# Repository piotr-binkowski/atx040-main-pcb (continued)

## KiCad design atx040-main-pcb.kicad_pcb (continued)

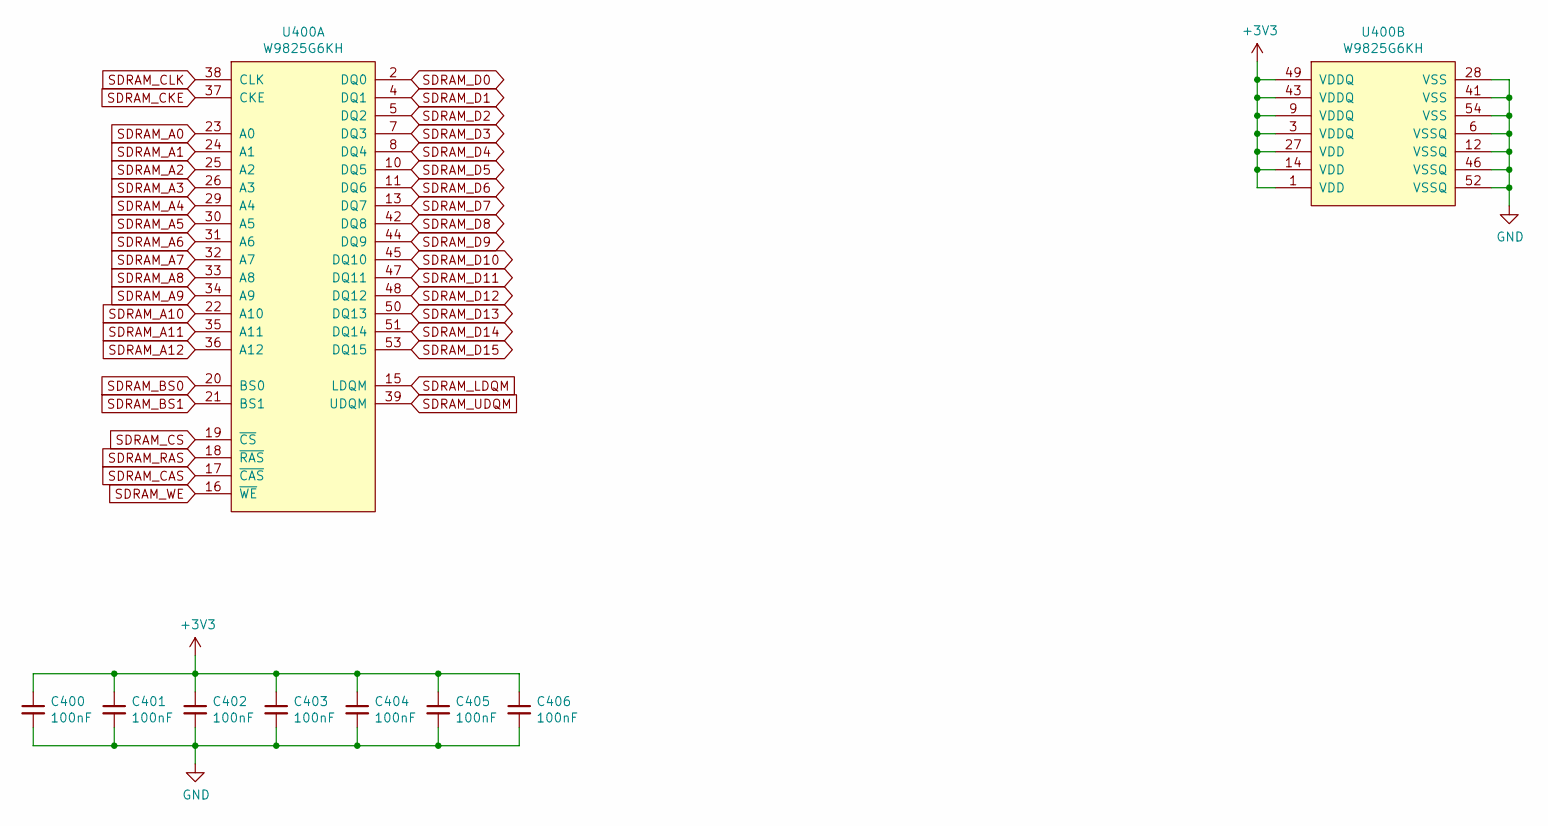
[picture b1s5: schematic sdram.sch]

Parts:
C400, C401, C402, C403, C404, C405, C406: 100nF; C_0603_1608Metric
U400: W9825G6KH; TSOP-II-54_22.2x10.16mm_P0.8mm; LCSC C26393

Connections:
+3V3: C400.1, C401.1, C402.1, C403.1, C404.1, C405.1, C406.1, U400.1 (VDD), U400.3 (VDDQ), U400.9 (VDDQ), U400.14 (VDD), U400.27 (VDD), U400.43 (VDDQ), U400.49 (VDDQ); also elsewhere on the board
GND: C400.2, C401.2, C402.2, C403.2, C404.2, C405.2, C406.2, U400.6 (VSSQ), U400.12 (VSSQ), U400.28 (VSS), U400.41 (VSS), U400.46 (VSSQ), U400.52 (VSSQ), U400.54 (VSS); also elsewhere on the board
SDRAM_A0: U400.23 (A0); also elsewhere on the board
SDRAM_A1: U400.24 (A1); also elsewhere on the board
SDRAM_A2: U400.25 (A2); also elsewhere on the board
SDRAM_A3: U400.26 (A3); also elsewhere on the board
SDRAM_A4: U400.29 (A4); also elsewhere on the board
SDRAM_A5: U400.30 (A5); also elsewhere on the board
SDRAM_A6: U400.31 (A6); also elsewhere on the board
SDRAM_A7: U400.32 (A7); also elsewhere on the board
SDRAM_A8: U400.33 (A8); also elsewhere on the board
SDRAM_A9: U400.34 (A9); also elsewhere on the board
SDRAM_A10: U400.22 (A10); also elsewhere on the board
SDRAM_A11: U400.35 (A11); also elsewhere on the board
SDRAM_A12: U400.36 (A12); also elsewhere on the board
SDRAM_BS0: U400.20 (BS0); also elsewhere on the board
SDRAM_BS1: U400.21 (BS1); also elsewhere on the board
SDRAM_CAS: U400.17 (~CAS); also elsewhere on the board
SDRAM_CKE: U400.37 (CKE); also elsewhere on the board
SDRAM_CLK: U400.38 (CLK); also elsewhere on the board
SDRAM_CS: U400.19 (~CS); also elsewhere on the board
SDRAM_D0: U400.2 (DQ0); also elsewhere on the board
SDRAM_D1: U400.4 (DQ1); also elsewhere on the board
SDRAM_D2: U400.5 (DQ2); also elsewhere on the board
SDRAM_D3: U400.7 (DQ3); also elsewhere on the board
SDRAM_D4: U400.8 (DQ4); also elsewhere on the board
SDRAM_D5: U400.10 (DQ5); also elsewhere on the board
SDRAM_D6: U400.11 (DQ6); also elsewhere on the board
SDRAM_D7: U400.13 (DQ7); also elsewhere on the board
SDRAM_D8: U400.42 (DQ8); also elsewhere on the board
SDRAM_D9: U400.44 (DQ9); also elsewhere on the board
SDRAM_D10: U400.45 (DQ10); also elsewhere on the board
SDRAM_D11: U400.47 (DQ11); also elsewhere on the board
SDRAM_D12: U400.48 (DQ12); also elsewhere on the board
SDRAM_D13: U400.50 (DQ13); also elsewhere on the board
SDRAM_D14: U400.51 (DQ14); also elsewhere on the board
SDRAM_D15: U400.53 (DQ15); also elsewhere on the board
SDRAM_LDQM: U400.15 (LDQM); also elsewhere on the board
SDRAM_RAS: U400.18 (~RAS); also elsewhere on the board
SDRAM_UDQM: U400.39 (UDQM); also elsewhere on the board
SDRAM_WE: U400.16 (~WE); also elsewhere on the board

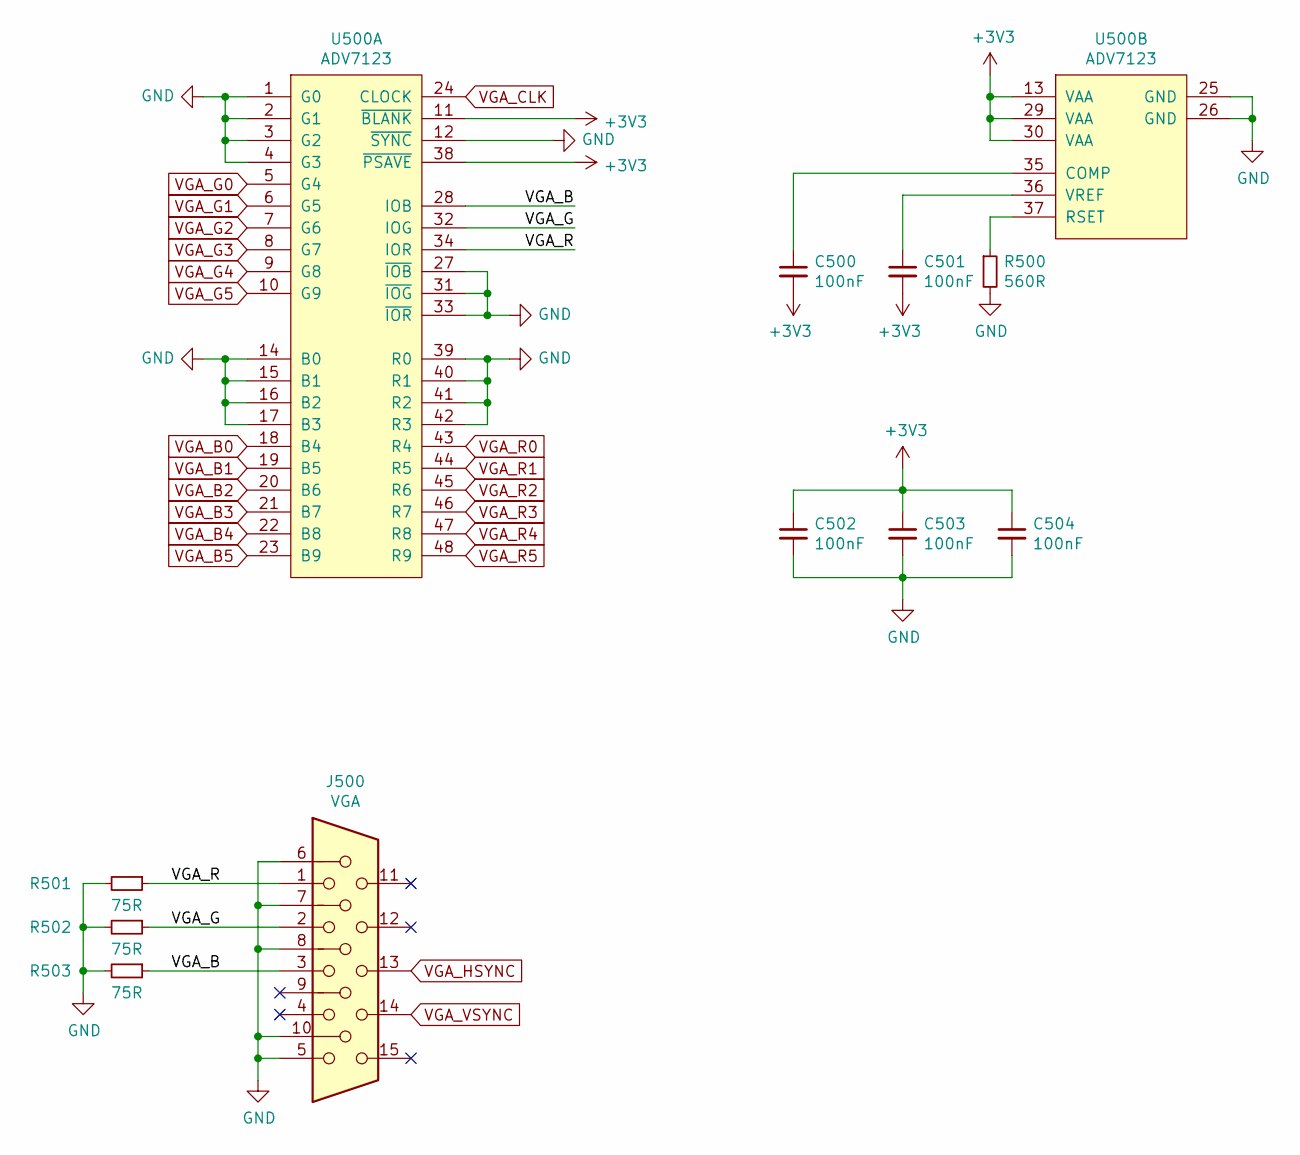
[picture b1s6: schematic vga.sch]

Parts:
C500, C501, C502, C503, C504: 100nF; C_0603_1608Metric
J500: VGA; DSUB-15-HD_Female_Horizontal_P2.29x1.98mm_EdgePinOffset3.03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
R500: 560R; R_0402_1005Metric
R501, R502, R503: 75R; R_0603_1608Metric
U500: ADV7123; LQFP-48_7x7mm_P0.5mm; LCSC C22234

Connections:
+3V3: C500.2, C501.2, C502.1, C503.1, C504.1, U500.11 (~BLANK), U500.13 (VAA), U500.29 (VAA), U500.30 (VAA), U500.38 (~PSAVE); also elsewhere on the board
/VGA Output/VGA_B: J500.3, R503.1, U500.28 (IOB)
/VGA Output/VGA_G: J500.2, R502.1, U500.32 (IOG)
/VGA Output/VGA_R: J500.1, R501.1, U500.34 (IOR)
GND: C502.2, C503.2, C504.2, J500.5, J500.6, J500.7, J500.8, J500.10, R500.2, R501.2, R502.2, R503.2, U500.1 (G0), U500.2 (G1), U500.3 (G2), U500.4 (G3), U500.12 (~SYNC), U500.14 (B0), U500.15 (B1), U500.16 (B2), U500.17 (B3), U500.25 (GND), U500.26 (GND), U500.27 (~IOB), U500.31 (~IOG), U500.33 (~IOR), U500.39 (R0), U500.40 (R1), U500.41 (R2), U500.42 (R3); also elsewhere on the board
unnamed: C500.1, U500.35 (COMP)
unnamed: C501.1, U500.36 (VREF)
unnamed: R500.1, U500.37 (RSET)
VGA_B0: U500.18 (B4); also elsewhere on the board
VGA_B1: U500.19 (B5); also elsewhere on the board
VGA_B2: U500.20 (B6); also elsewhere on the board
VGA_B3: U500.21 (B7); also elsewhere on the board
VGA_B4: U500.22 (B8); also elsewhere on the board
VGA_B5: U500.23 (B9); also elsewhere on the board
VGA_CLK: U500.24 (CLOCK); also elsewhere on the board
VGA_G0: U500.5 (G4); also elsewhere on the board
VGA_G1: U500.6 (G5); also elsewhere on the board
VGA_G2: U500.7 (G6); also elsewhere on the board
VGA_G3: U500.8 (G7); also elsewhere on the board
VGA_G4: U500.9 (G8); also elsewhere on the board
VGA_G5: U500.10 (G9); also elsewhere on the board
VGA_HSYNC: J500.13; also elsewhere on the board
VGA_R0: U500.43 (R4); also elsewhere on the board
VGA_R1: U500.44 (R5); also elsewhere on the board
VGA_R2: U500.45 (R6); also elsewhere on the board
VGA_R3: U500.46 (R7); also elsewhere on the board
VGA_R4: U500.47 (R8); also elsewhere on the board
VGA_R5: U500.48 (R9); also elsewhere on the board
VGA_VSYNC: J500.14; also elsewhere on the board

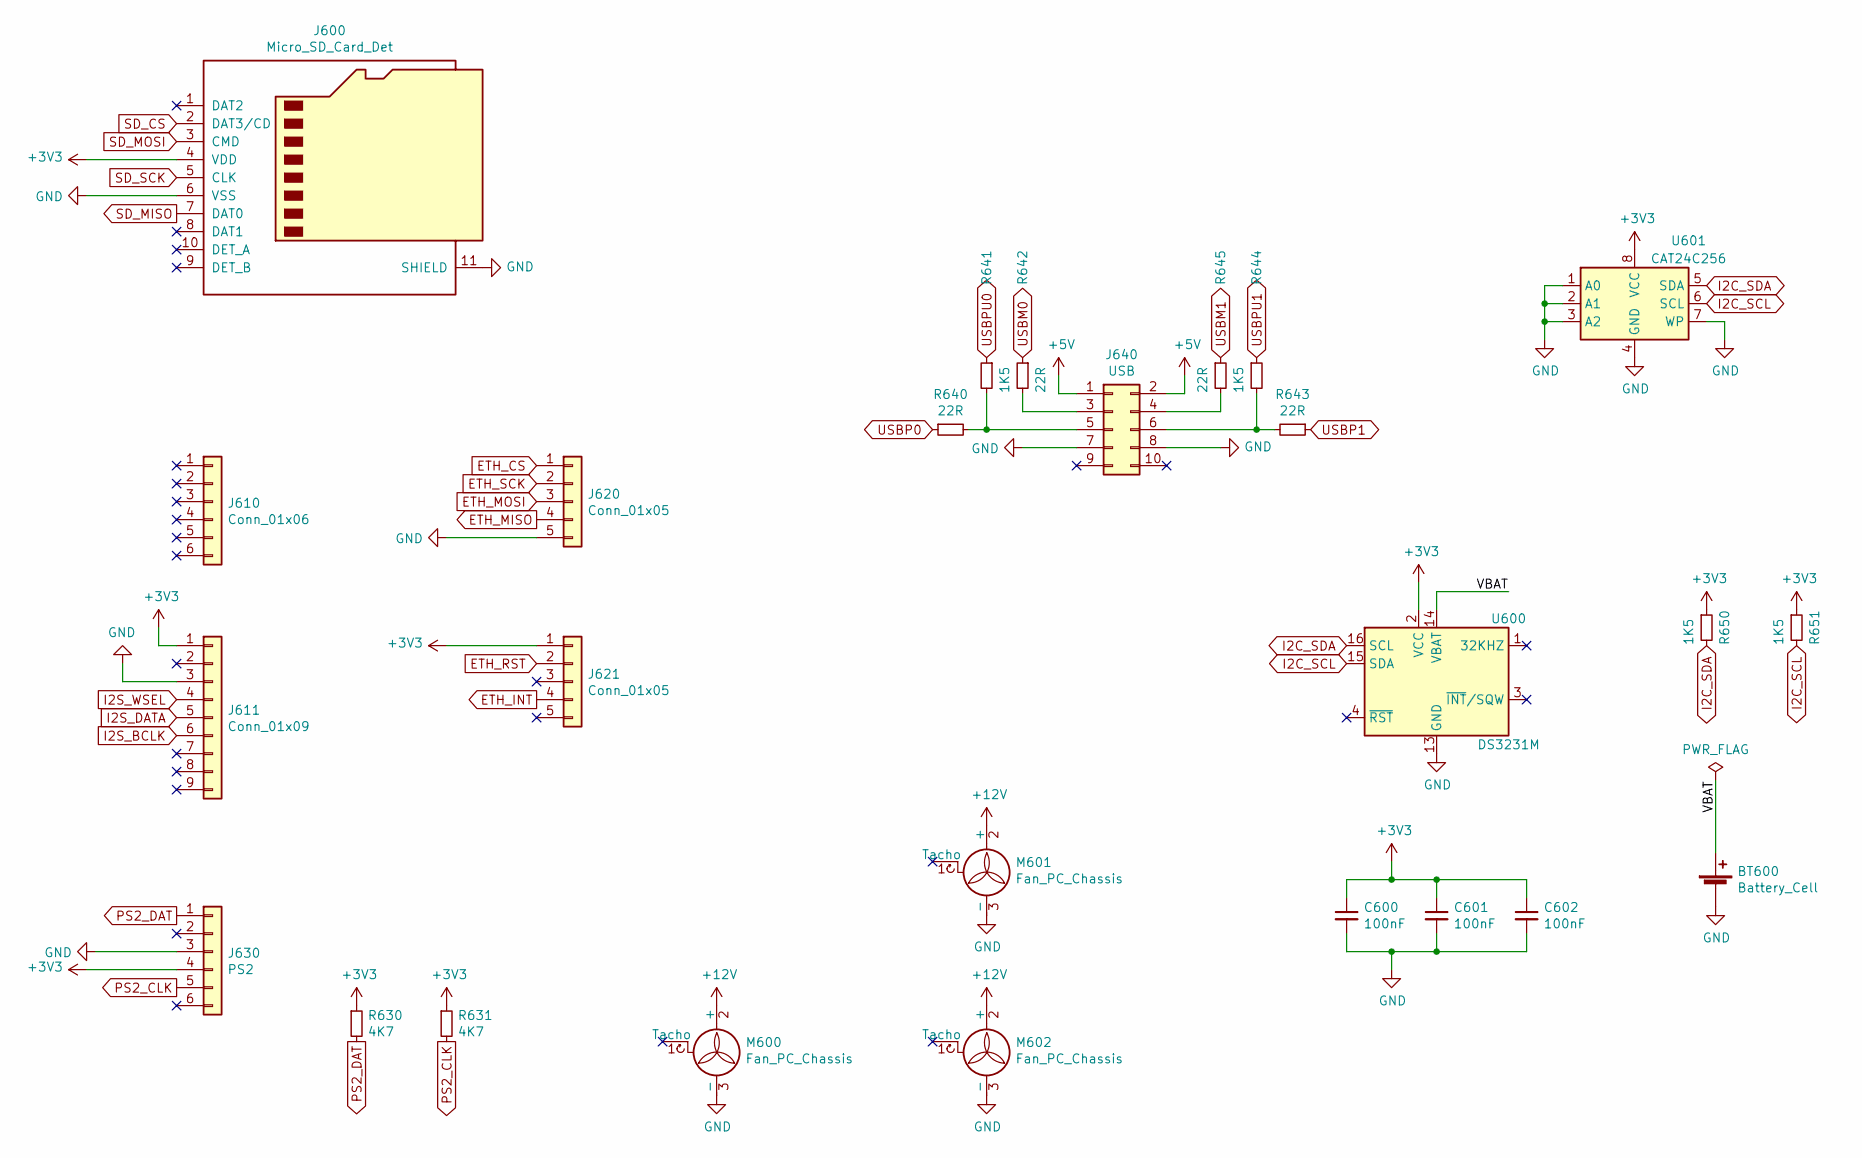
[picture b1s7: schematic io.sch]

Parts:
BT600: Battery_Cell; BatteryHolder_Keystone_1060_1x2032
C600, C601, C602: 100nF; C_0603_1608Metric
J600: Micro_SD_Card_Det; microSD_HC_Molex_104031-0811
J610: Conn_01x06; PinSocket_1x06_P2.54mm_Vertical
J611: Conn_01x09; PinSocket_1x09_P2.54mm_Vertical
J620, J621: Conn_01x05; PinSocket_1x05_P2.54mm_Vertical
J630: PS2; KMDTX-HT-6S-BSC
J640: USB; PinHeader_2x05_P2.54mm_Vertical
M600, M601, M602: Fan_PC_Chassis; FanPinHeader_1x03_P2.54mm_Vertical
R630, R631: 4K7; R_0603_1608Metric
R640, R642, R643, R645: 22R; R_0603_1608Metric
R641, R644, R650, R651: 1K5; R_0603_1608Metric
U600: DS3231M; SOIC-16W_7.5x10.3mm_P1.27mm
U601: CAT24C256; SOIC-8_3.9x4.9mm_P1.27mm

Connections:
+3V3: C600.1, C601.1, C602.1, J600.4 (VDD), J611.1, J621.1, J630.4, R630.1, R631.1, R650.1, R651.1, U600.2 (VCC), U601.8 (VCC); also elsewhere on the board
+5V: J640.1, J640.2; also elsewhere on the board
+12V: M600.2 (+), M601.2 (+), M602.2 (+); also elsewhere on the board
/Misc IO/VBAT: BT600.1 (+), U600.14 (VBAT)
ETH_CS: J620.1; also elsewhere on the board
ETH_INT: J621.4; also elsewhere on the board
ETH_MISO: J620.4; also elsewhere on the board
ETH_MOSI: J620.3; also elsewhere on the board
ETH_RST: J621.2; also elsewhere on the board
ETH_SCK: J620.2; also elsewhere on the board
GND: BT600.2 (-), C600.2, C601.2, C602.2, J600.6 (VSS), J600.11 (SHIELD), J611.3, J620.5, J630.3, J640.7, J640.8, M600.3 (-), M601.3 (-), M602.3 (-), U600.5 (GND), U600.6 (GND), U600.7 (GND), U600.8 (GND), U600.9 (GND), U600.10 (GND), U600.11 (GND), U600.12 (GND), U600.13 (GND), U601.1 (A0), U601.2 (A1), U601.3 (A2), U601.4 (GND), U601.7 (WP); also elsewhere on the board
I2C_SCL: R651.2, U600.15 (SDA), U601.6 (SCL); also elsewhere on the board
I2C_SDA: R650.2, U600.16 (SCL), U601.5 (SDA); also elsewhere on the board
I2S_BCLK: J611.6; also elsewhere on the board
I2S_DATA: J611.5; also elsewhere on the board
I2S_WSEL: J611.4; also elsewhere on the board
unnamed: J640.3, R642.2
unnamed: J640.4, R645.2
unnamed: J640.5, R640.2, R641.2
unnamed: J640.6, R643.2, R644.2
PS2_CLK: J630.5, R631.2; also elsewhere on the board
PS2_DAT: J630.1, R630.2; also elsewhere on the board
SD_CS: J600.2 (DAT3/CD); also elsewhere on the board
SD_MISO: J600.7 (DAT0); also elsewhere on the board
SD_MOSI: J600.3 (CMD); also elsewhere on the board
SD_SCK: J600.5 (CLK); also elsewhere on the board
USBM0: R642.1; also elsewhere on the board
USBM1: R645.1; also elsewhere on the board
USBP0: R640.1; also elsewhere on the board
USBP1: R643.1; also elsewhere on the board
USBPU0: R641.1; also elsewhere on the board
USBPU1: R644.1; also elsewhere on the board

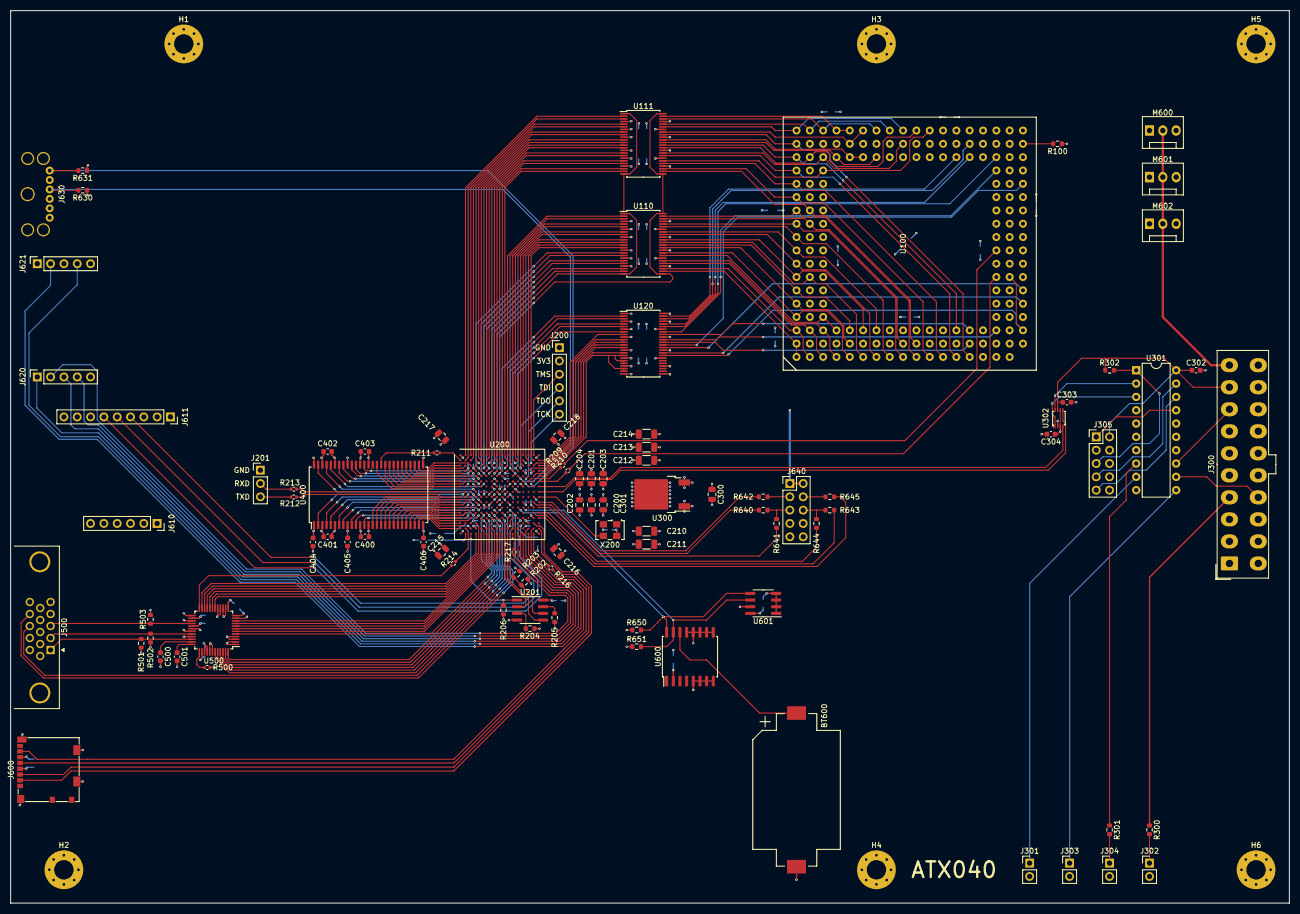
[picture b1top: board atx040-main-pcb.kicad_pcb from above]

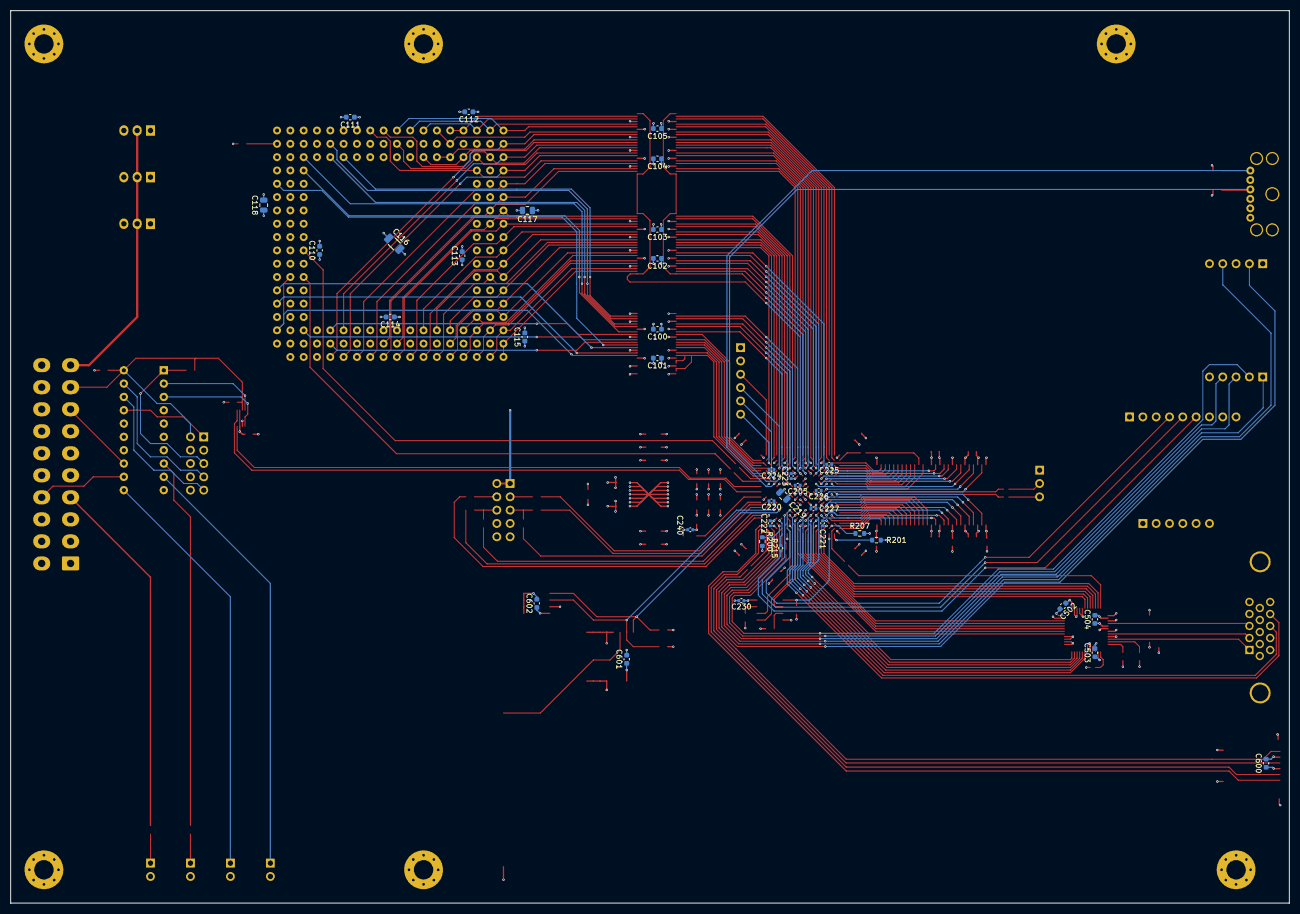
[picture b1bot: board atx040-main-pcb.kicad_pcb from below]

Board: 4 copper layers, 243.8 x 170.2 mm, 136 parts (37 on the bottom side), 233 nets.

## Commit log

2021-01-17 Finished board + fab files
